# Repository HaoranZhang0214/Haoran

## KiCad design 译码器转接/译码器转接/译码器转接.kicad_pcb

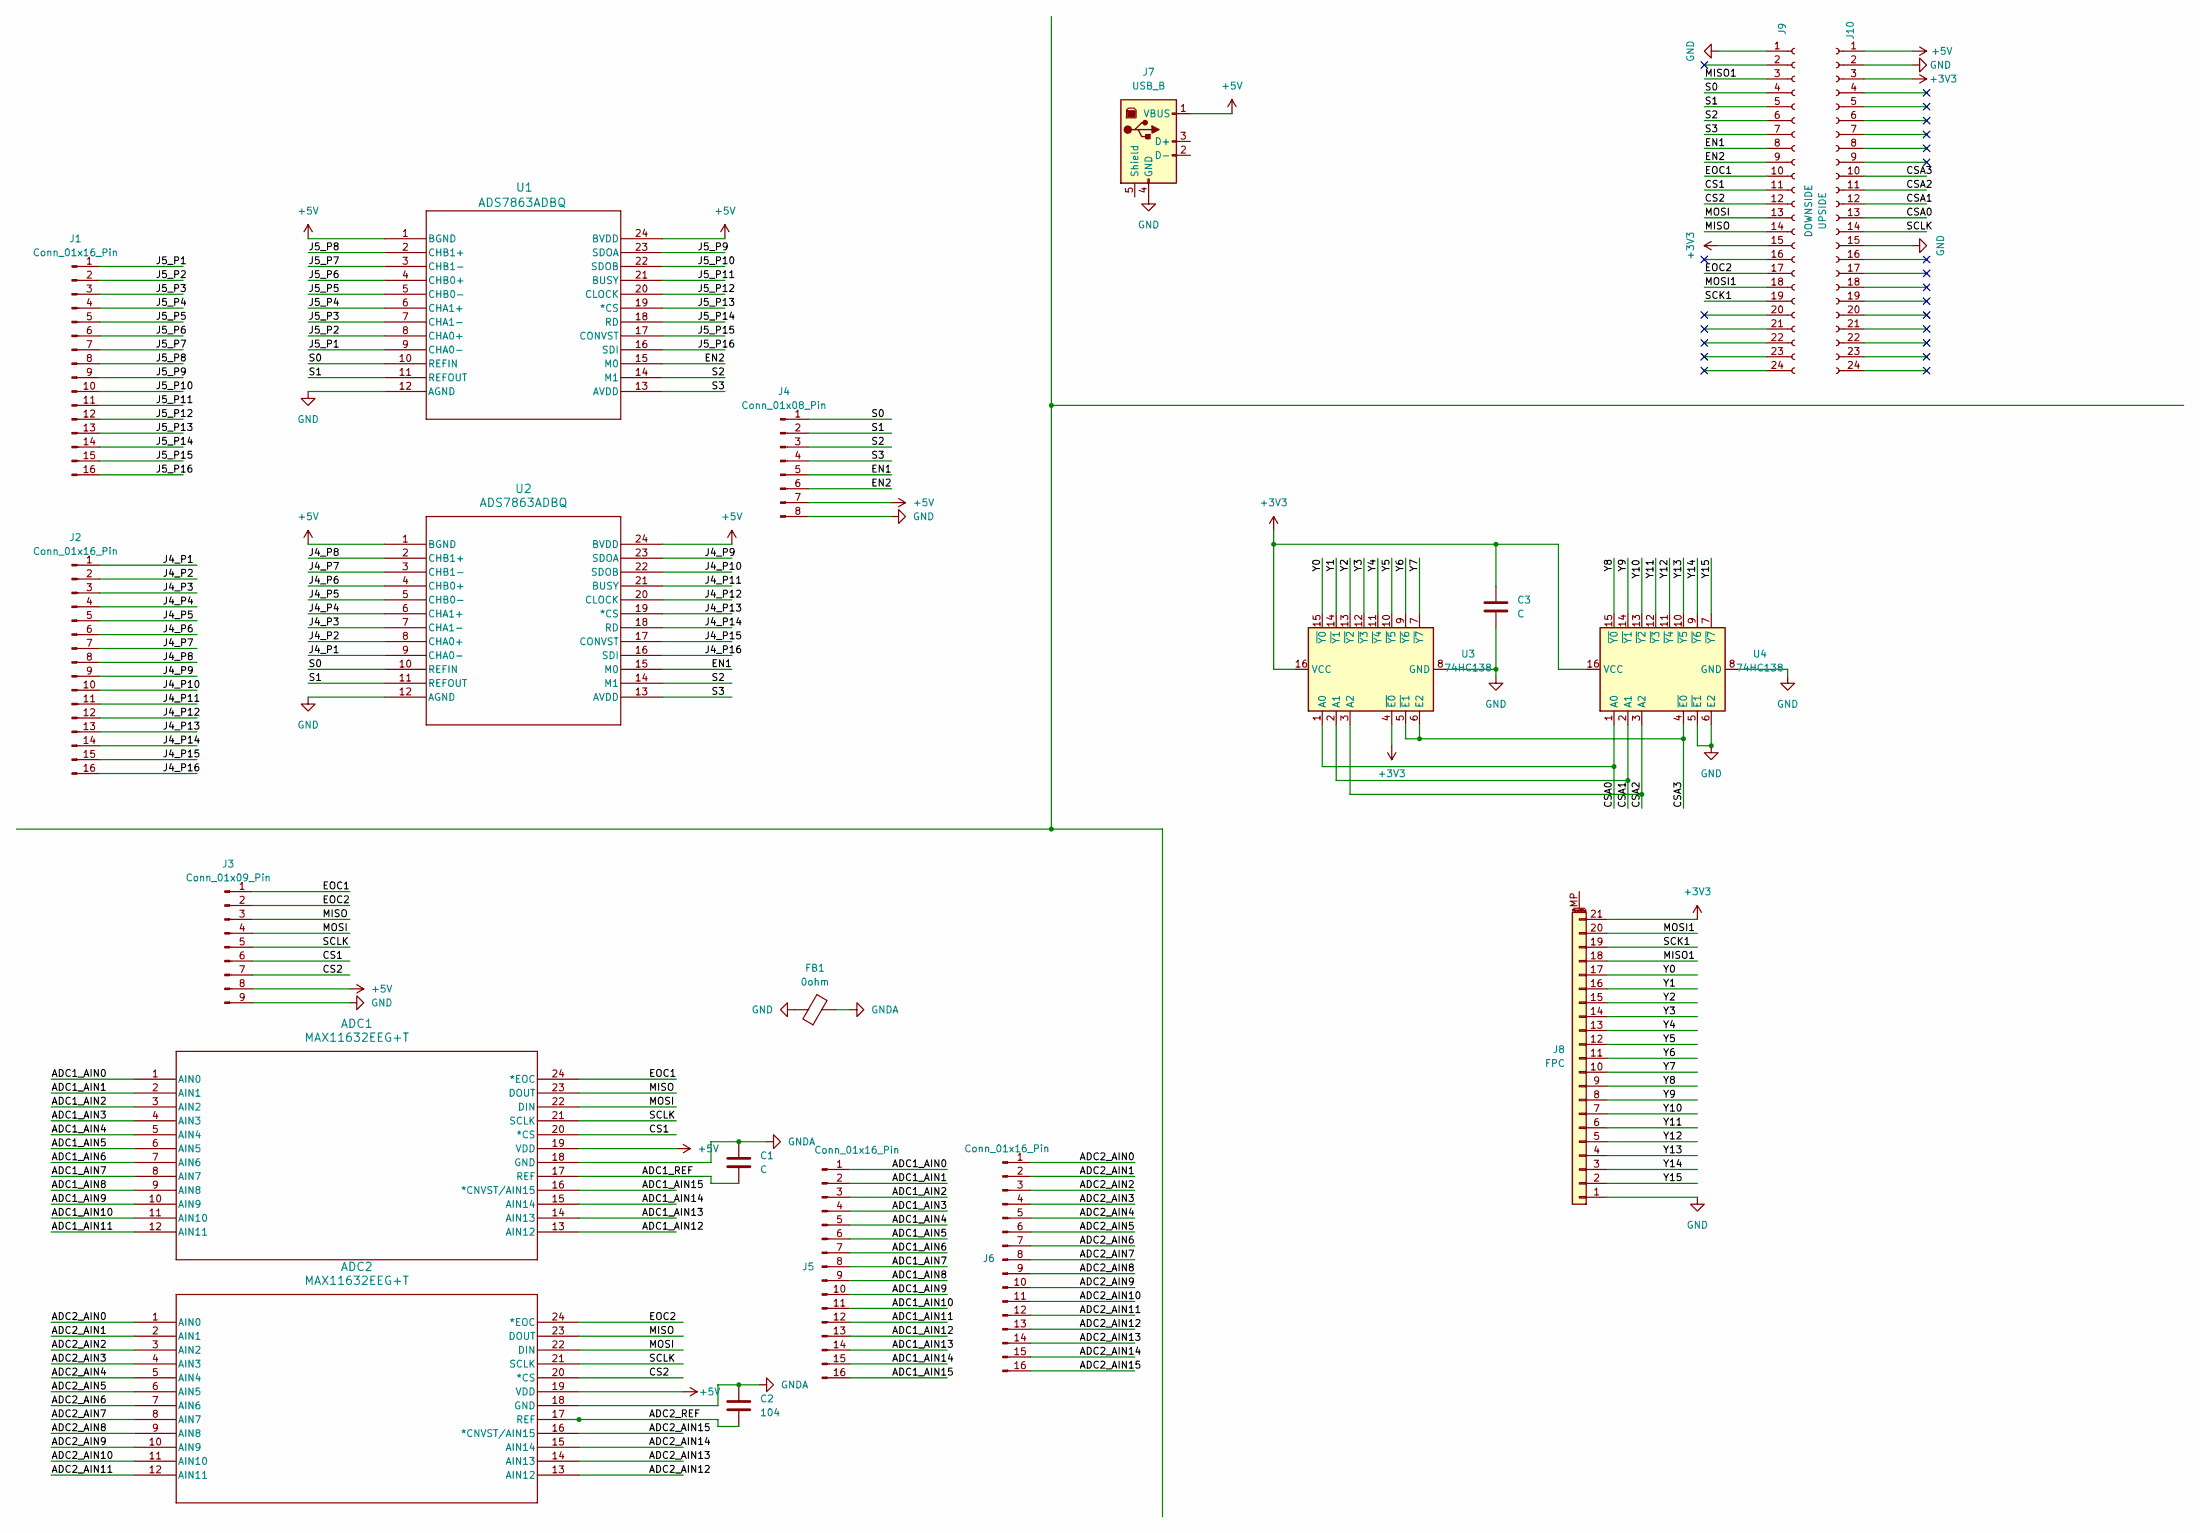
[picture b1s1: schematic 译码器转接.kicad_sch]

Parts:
ADC1, ADC2: MAX11632EEG+T; 21-0055H_24_MXM
C1, C3: C; C_0805_2012Metric_Pad1.18x1.45mm_HandSolder
C2: 104; C_0805_2012Metric_Pad1.18x1.45mm_HandSolder
FB1: 0ohm; L_0805_2012Metric_Pad1.05x1.20mm_HandSolder
J1, J2, J5, J6: Conn_01x16_Pin; PinHeader_1x16_P2.54mm_Vertical
J3: Conn_01x09_Pin; PinHeader_1x09_P2.54mm_Vertical
J4: Conn_01x08_Pin; PinHeader_1x08_P2.54mm_Vertical
J7: USB_B; USB_B_Lumberg_2411_02_Horizontal
J8: FPC; TE_2-84952-1_1x21-1MP_P1.0mm_Horizontal
J9: DOWNSIDE; PinSocket_1x24_P2.54mm_Vertical
J10: UPSIDE; PinSocket_1x24_P2.54mm_Vertical
U1, U2: ADS7863ADBQ; SSOP-24_5.3x8.2mm_P0.65mm
U3, U4: 74HC138; SOIC-16_3.9x9.9mm_P1.27mm

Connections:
+3V3: C3.1, J8.21, J9.15, J10.3, U3.4 (~E0), U3.16 (VCC), U4.16 (VCC)
+5V: ADC1.19 (VDD), ADC2.19 (VDD), J3.8, J4.7, J7.1 (VBUS), J10.1, U1.1 (BGND), U1.24 (BVDD), U2.1 (BGND), U2.24 (BVDD)
/ADC1_AIN0: ADC1.1 (AIN0), J5.1; also elsewhere on the board
/ADC1_AIN1: ADC1.2 (AIN1), J5.2; also elsewhere on the board
/ADC1_AIN2: ADC1.3 (AIN2), J5.3; also elsewhere on the board
/ADC1_AIN3: ADC1.4 (AIN3), J5.4; also elsewhere on the board
/ADC1_AIN4: ADC1.5 (AIN4), J5.5; also elsewhere on the board
/ADC1_AIN5: ADC1.6 (AIN5), J5.6; also elsewhere on the board
/ADC1_AIN6: ADC1.7 (AIN6), J5.7; also elsewhere on the board
/ADC1_AIN7: ADC1.8 (AIN7), J5.8; also elsewhere on the board
/ADC1_AIN8: ADC1.9 (AIN8), J5.9; also elsewhere on the board
/ADC1_AIN9: ADC1.10 (AIN9), J5.10; also elsewhere on the board
/ADC1_AIN10: ADC1.11 (AIN10), J5.11; also elsewhere on the board
/ADC1_AIN11: ADC1.12 (AIN11), J5.12; also elsewhere on the board
/ADC1_AIN12: ADC1.13 (AIN12), J5.13; also elsewhere on the board
/ADC1_AIN13: ADC1.14 (AIN13), J5.14; also elsewhere on the board
/ADC1_AIN14: ADC1.15 (AIN14), J5.15; also elsewhere on the board
/ADC1_AIN15: ADC1.16 (*CNVST/AIN15), J5.16; also elsewhere on the board
/ADC1_REF: ADC1.17 (REF), C1.1
/ADC2_AIN0: ADC2.1 (AIN0), J6.1; also elsewhere on the board
/ADC2_AIN1: ADC2.2 (AIN1), J6.2; also elsewhere on the board
/ADC2_AIN2: ADC2.3 (AIN2), J6.3; also elsewhere on the board
/ADC2_AIN3: ADC2.4 (AIN3), J6.4; also elsewhere on the board
/ADC2_AIN4: ADC2.5 (AIN4), J6.5; also elsewhere on the board
/ADC2_AIN5: ADC2.6 (AIN5), J6.6; also elsewhere on the board
/ADC2_AIN6: ADC2.7 (AIN6), J6.7; also elsewhere on the board
/ADC2_AIN7: ADC2.8 (AIN7), J6.8; also elsewhere on the board
/ADC2_AIN8: ADC2.9 (AIN8), J6.9; also elsewhere on the board
/ADC2_AIN9: ADC2.10 (AIN9), J6.10; also elsewhere on the board
/ADC2_AIN10: ADC2.11 (AIN10), J6.11; also elsewhere on the board
/ADC2_AIN11: ADC2.12 (AIN11), J6.12; also elsewhere on the board
/ADC2_AIN12: ADC2.13 (AIN12), J6.13; also elsewhere on the board
/ADC2_AIN13: ADC2.14 (AIN13), J6.14; also elsewhere on the board
/ADC2_AIN14: ADC2.15 (AIN14), J6.15; also elsewhere on the board
/ADC2_AIN15: ADC2.16 (*CNVST/AIN15), J6.16; also elsewhere on the board
/ADC2_REF: ADC2.17 (REF), C2.1
/CS1: ADC1.20 (*CS), J3.6, J9.11
/CS2: ADC2.20 (*CS), J3.7, J9.12
/CSA0: J10.13, U3.1 (A0), U4.1 (A0)
/CSA1: J10.12, U3.2 (A1), U4.2 (A1)
/CSA2: J10.11, U3.3 (A2), U4.3 (A2)
/CSA3: J10.10, U3.5 (~E1), U3.6 (E2), U4.4 (~E0)
/EN1: J4.5, J9.8, U2.15 (M0)
/EN2: J4.6, J9.9, U1.15 (M0)
/EOC1: ADC1.24 (*EOC), J3.1, J9.10
/EOC2: ADC2.24 (*EOC), J3.2, J9.17
/J4_P1: J2.1, U2.9 (CHA0-)
/J4_P2: J2.2, U2.8 (CHA0+)
/J4_P3: J2.3, U2.7 (CHA1-)
/J4_P4: J2.4, U2.6 (CHA1+)
/J4_P5: J2.5, U2.5 (CHB0-)
/J4_P6: J2.6, U2.4 (CHB0+)
/J4_P7: J2.7, U2.3 (CHB1-)
/J4_P8: J2.8, U2.2 (CHB1+)
/J4_P9: J2.9, U2.23 (SDOA)
/J4_P10: J2.10, U2.22 (SDOB)
/J4_P11: J2.11, U2.21 (BUSY)
/J4_P12: J2.12, U2.20 (CLOCK)
/J4_P13: J2.13, U2.19 (*CS)
/J4_P14: J2.14, U2.18 (RD)
/J4_P15: J2.15, U2.17 (CONVST)
/J4_P16: J2.16, U2.16 (SDI)
/J5_P1: J1.1, U1.9 (CHA0-)
/J5_P2: J1.2, U1.8 (CHA0+)
/J5_P3: J1.3, U1.7 (CHA1-)
/J5_P4: J1.4, U1.6 (CHA1+)
/J5_P5: J1.5, U1.5 (CHB0-)
/J5_P6: J1.6, U1.4 (CHB0+)
/J5_P7: J1.7, U1.3 (CHB1-)
/J5_P8: J1.8, U1.2 (CHB1+)
/J5_P9: J1.9, U1.23 (SDOA)
/J5_P10: J1.10, U1.22 (SDOB)
/J5_P11: J1.11, U1.21 (BUSY)
/J5_P12: J1.12, U1.20 (CLOCK)
/J5_P13: J1.13, U1.19 (*CS)
/J5_P14: J1.14, U1.18 (RD)
/J5_P15: J1.15, U1.17 (CONVST)
/J5_P16: J1.16, U1.16 (SDI)
/MISO: ADC1.23 (DOUT), ADC2.23 (DOUT), J3.3, J9.14
/MISO1: J8.18, J9.3
/MOSI: ADC1.22 (DIN), ADC2.22 (DIN), J3.4, J9.13
/MOSI1: J8.20, J9.18
/S0: J4.1, J9.4, U1.10 (REFIN), U2.10 (REFIN)
/S1: J4.2, J9.5, U1.11 (REFOUT), U2.11 (REFOUT)
/S2: J4.3, J9.6, U1.14 (M1), U2.14 (M1)
/S3: J4.4, J9.7, U1.13 (AVDD), U2.13 (AVDD)
/SCK1: J8.19, J9.19
/SCLK: ADC1.21 (SCLK), ADC2.21 (SCLK), J3.5, J10.14
/Y0: J8.17, U3.15 (~Y0)
/Y1: J8.16, U3.14 (~Y1)
/Y2: J8.15, U3.13 (~Y2)
/Y3: J8.14, U3.12 (~Y3)
/Y4: J8.13, U3.11 (~Y4)
/Y5: J8.12, U3.10 (~Y5)
/Y6: J8.11, U3.9 (~Y6)
/Y7: J8.10, U3.7 (~Y7)
/Y8: J8.9, U4.15 (~Y0)
/Y9: J8.8, U4.14 (~Y1)
/Y10: J8.7, U4.13 (~Y2)
/Y11: J8.6, U4.12 (~Y3)
/Y12: J8.5, U4.11 (~Y4)
/Y13: J8.4, U4.10 (~Y5)
/Y14: J8.3, U4.9 (~Y6)
/Y15: J8.2, U4.7 (~Y7)
GND: C3.2, FB1.1, J3.9, J4.8, J7.4 (GND), J8.1, J9.1, J10.2, J10.15, U1.12 (AGND), U2.12 (AGND), U3.8 (GND), U4.5 (~E1), U4.6 (E2), U4.8 (GND)
GNDA: ADC1.18 (GND), ADC2.18 (GND), C1.2, C2.2, FB1.2

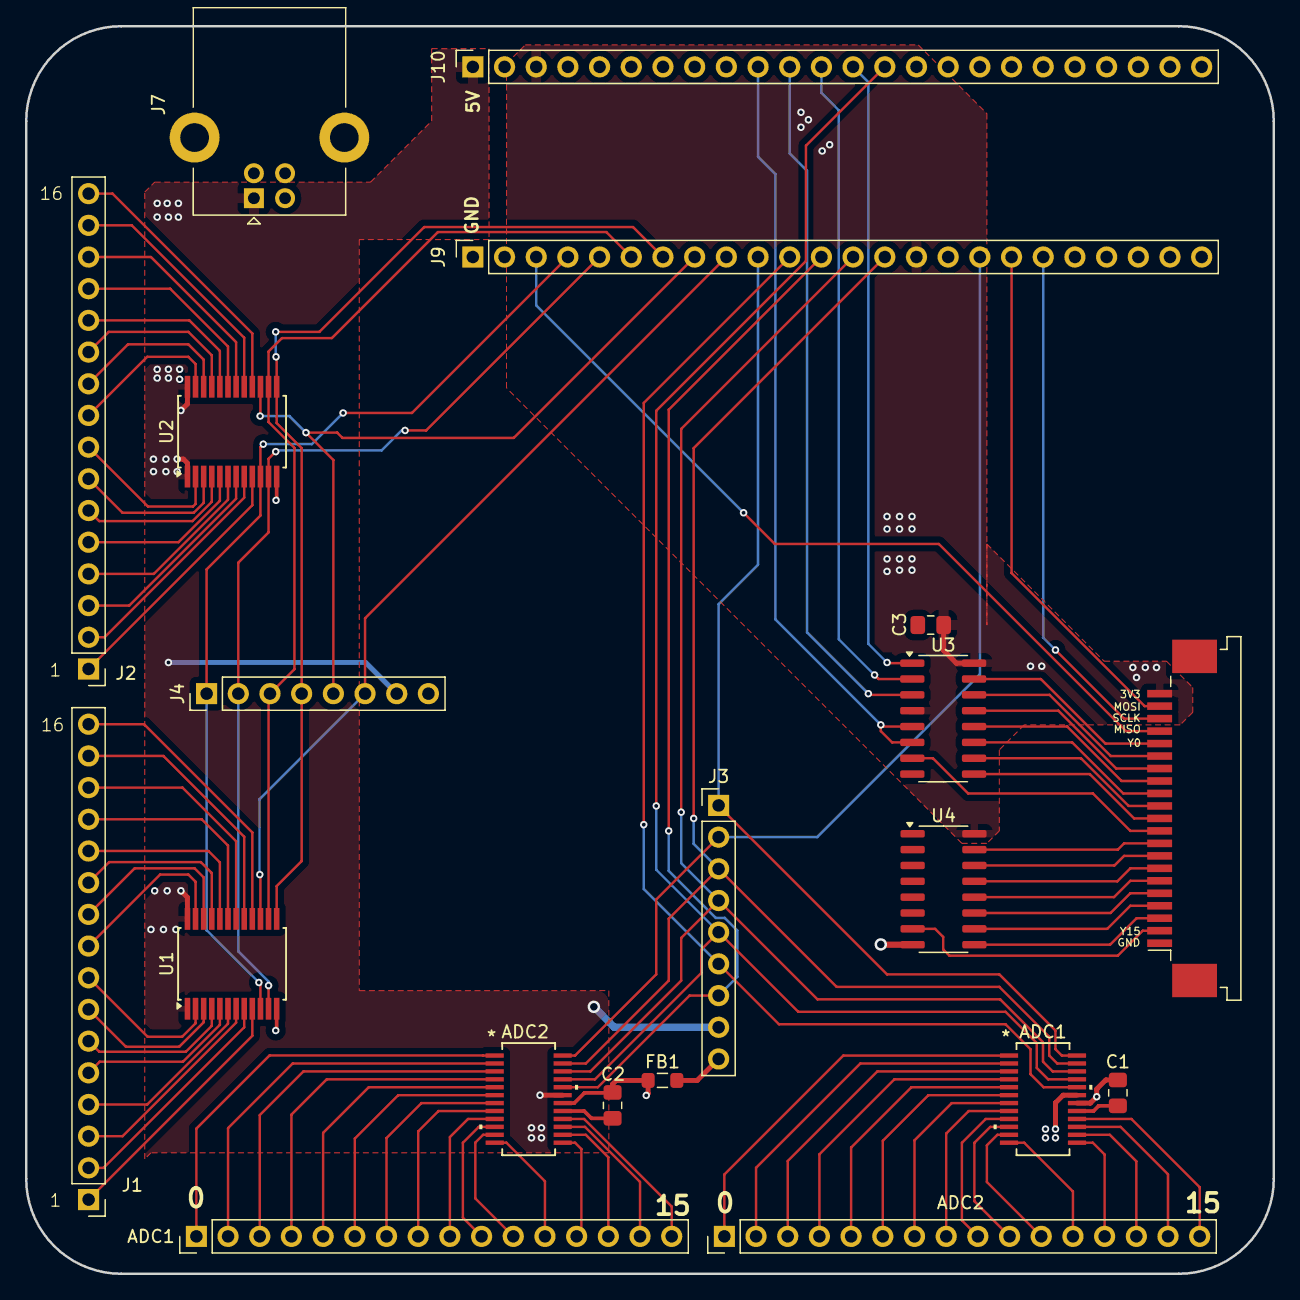
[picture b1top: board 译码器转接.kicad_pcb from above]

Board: 2 copper layers, 100.0 x 100.0 mm, 20 parts (0 on the bottom side), 106 nets.

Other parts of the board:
ADC1#2, ADC2#2: Conn_01x16_Pin; PinHeader_1x16_P2.54mm_Vertical

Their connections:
/ADC1_AIN0: ADC2#2.1; also elsewhere on the board
/ADC1_AIN1: ADC2#2.2; also elsewhere on the board
/ADC1_AIN2: ADC2#2.3; also elsewhere on the board
/ADC1_AIN3: ADC2#2.4; also elsewhere on the board
/ADC1_AIN4: ADC2#2.5; also elsewhere on the board
/ADC1_AIN5: ADC2#2.6; also elsewhere on the board
/ADC1_AIN6: ADC2#2.7; also elsewhere on the board
/ADC1_AIN7: ADC2#2.8; also elsewhere on the board
/ADC1_AIN8: ADC2#2.9; also elsewhere on the board
/ADC1_AIN9: ADC2#2.10; also elsewhere on the board
/ADC1_AIN10: ADC2#2.11; also elsewhere on the board
/ADC1_AIN11: ADC2#2.12; also elsewhere on the board
/ADC1_AIN12: ADC2#2.13; also elsewhere on the board
/ADC1_AIN13: ADC2#2.14; also elsewhere on the board
/ADC1_AIN14: ADC2#2.15; also elsewhere on the board
/ADC1_AIN15: ADC2#2.16; also elsewhere on the board
/ADC2_AIN0: ADC1#2.1; also elsewhere on the board
/ADC2_AIN1: ADC1#2.2; also elsewhere on the board
/ADC2_AIN2: ADC1#2.3; also elsewhere on the board
/ADC2_AIN3: ADC1#2.4; also elsewhere on the board
/ADC2_AIN4: ADC1#2.5; also elsewhere on the board
/ADC2_AIN5: ADC1#2.6; also elsewhere on the board
/ADC2_AIN6: ADC1#2.7; also elsewhere on the board
/ADC2_AIN7: ADC1#2.8; also elsewhere on the board
/ADC2_AIN8: ADC1#2.9; also elsewhere on the board
/ADC2_AIN9: ADC1#2.10; also elsewhere on the board
/ADC2_AIN10: ADC1#2.11; also elsewhere on the board
/ADC2_AIN11: ADC1#2.12; also elsewhere on the board
/ADC2_AIN12: ADC1#2.13; also elsewhere on the board
/ADC2_AIN13: ADC1#2.14; also elsewhere on the board
/ADC2_AIN14: ADC1#2.15; also elsewhere on the board
/ADC2_AIN15: ADC1#2.16; also elsewhere on the board

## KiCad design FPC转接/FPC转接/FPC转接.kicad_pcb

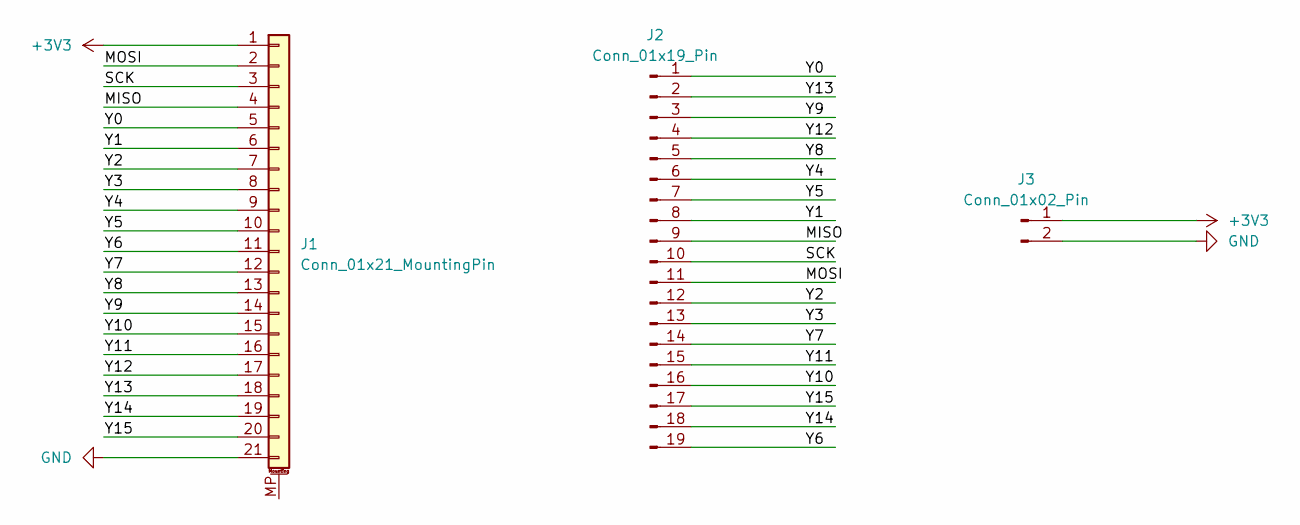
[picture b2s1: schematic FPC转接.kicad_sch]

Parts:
J1: Conn_01x21_MountingPin; TE_2-84952-1_1x21-1MP_P1.0mm_Horizontal
J2: Conn_01x19_Pin; PinHeader_1x19_P2.54mm_Vertical
J3: Conn_01x02_Pin; PinHeader_1x02_P2.54mm_Vertical

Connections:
+3V3: J1.1, J3.1
/MISO: J1.4, J2.9
/MOSI: J1.2, J2.11
/SCK: J1.3, J2.10
/Y0: J1.5, J2.1
/Y1: J1.6, J2.8
/Y2: J1.7, J2.12
/Y3: J1.8, J2.13
/Y4: J1.9, J2.6
/Y5: J1.10, J2.7
/Y6: J1.11, J2.19
/Y7: J1.12, J2.14
/Y8: J1.13, J2.5
/Y9: J1.14, J2.3
/Y10: J1.15, J2.16
/Y11: J1.16, J2.15
/Y12: J1.17, J2.4
/Y13: J1.18, J2.2
/Y14: J1.19, J2.18
/Y15: J1.20, J2.17
GND: J1.21, J3.2

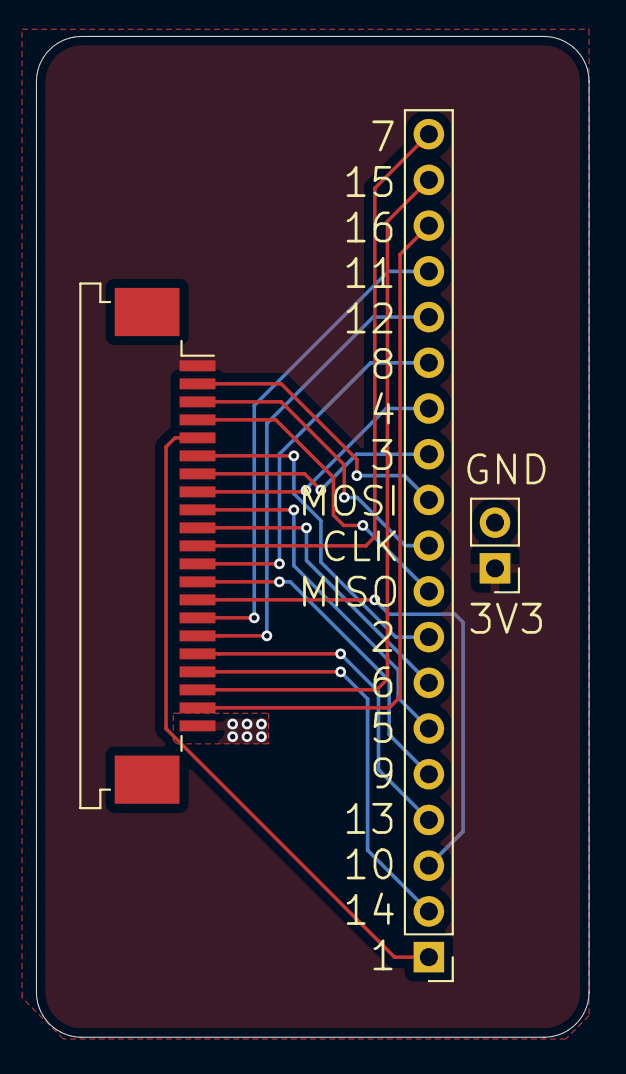
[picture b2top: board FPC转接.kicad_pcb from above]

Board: 2 copper layers, 30.7 x 55.6 mm, 3 parts (0 on the bottom side), 21 nets.
